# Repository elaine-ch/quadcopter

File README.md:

## Vortex 2024 Drone project

Video of it flying: [https://photos.app.goo.gl/hCnUwj7Pyiz6dDBa6](https://photos.app.goo.gl/hCnUwj7Pyiz6dDBa6)

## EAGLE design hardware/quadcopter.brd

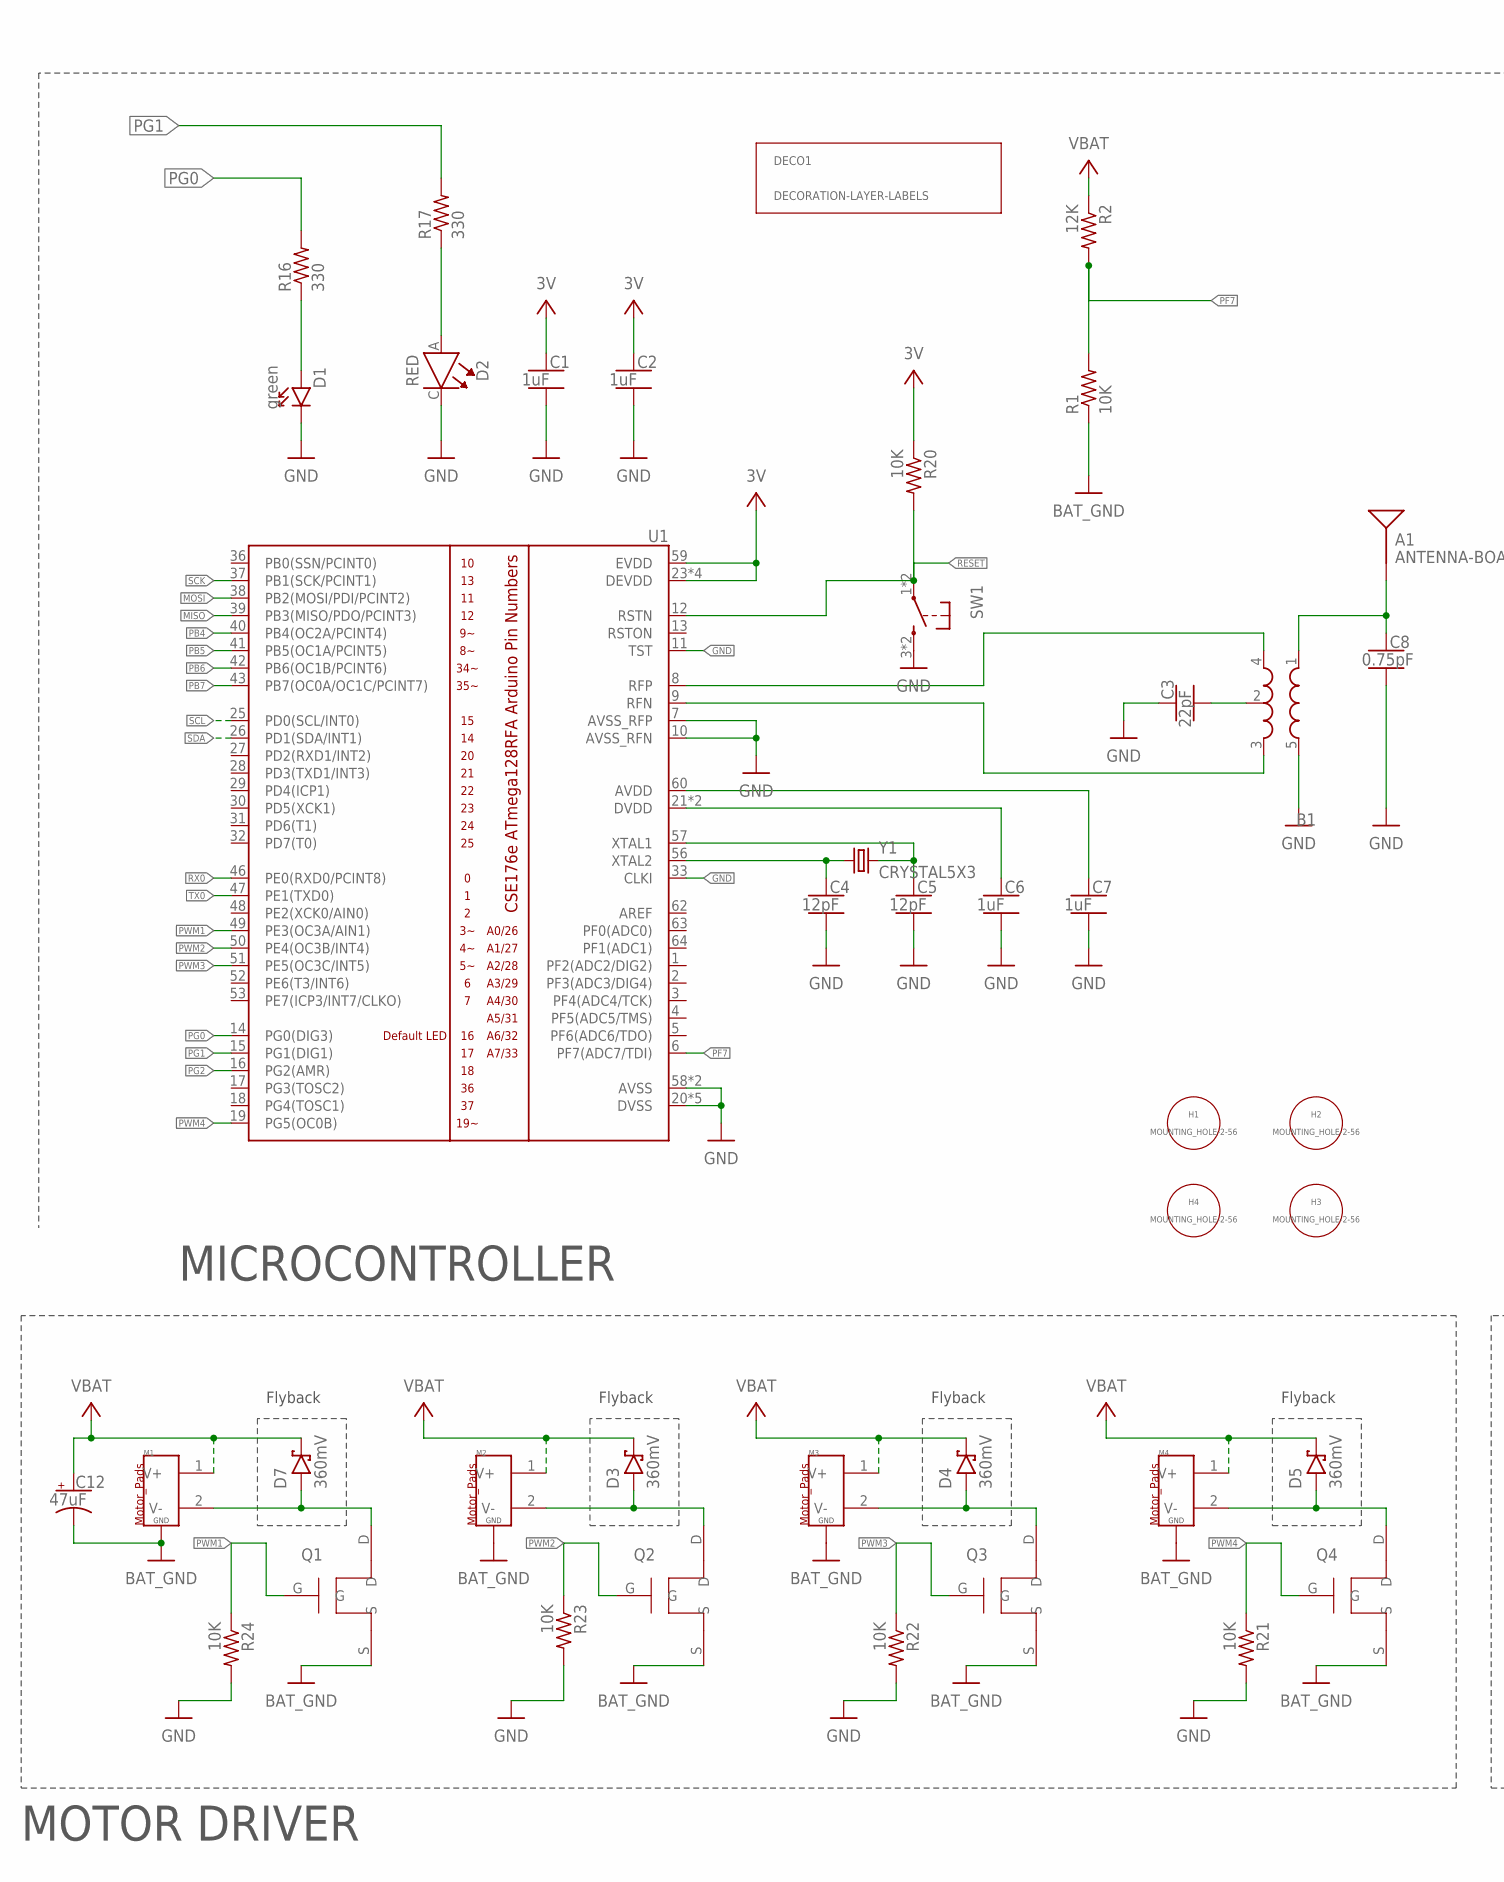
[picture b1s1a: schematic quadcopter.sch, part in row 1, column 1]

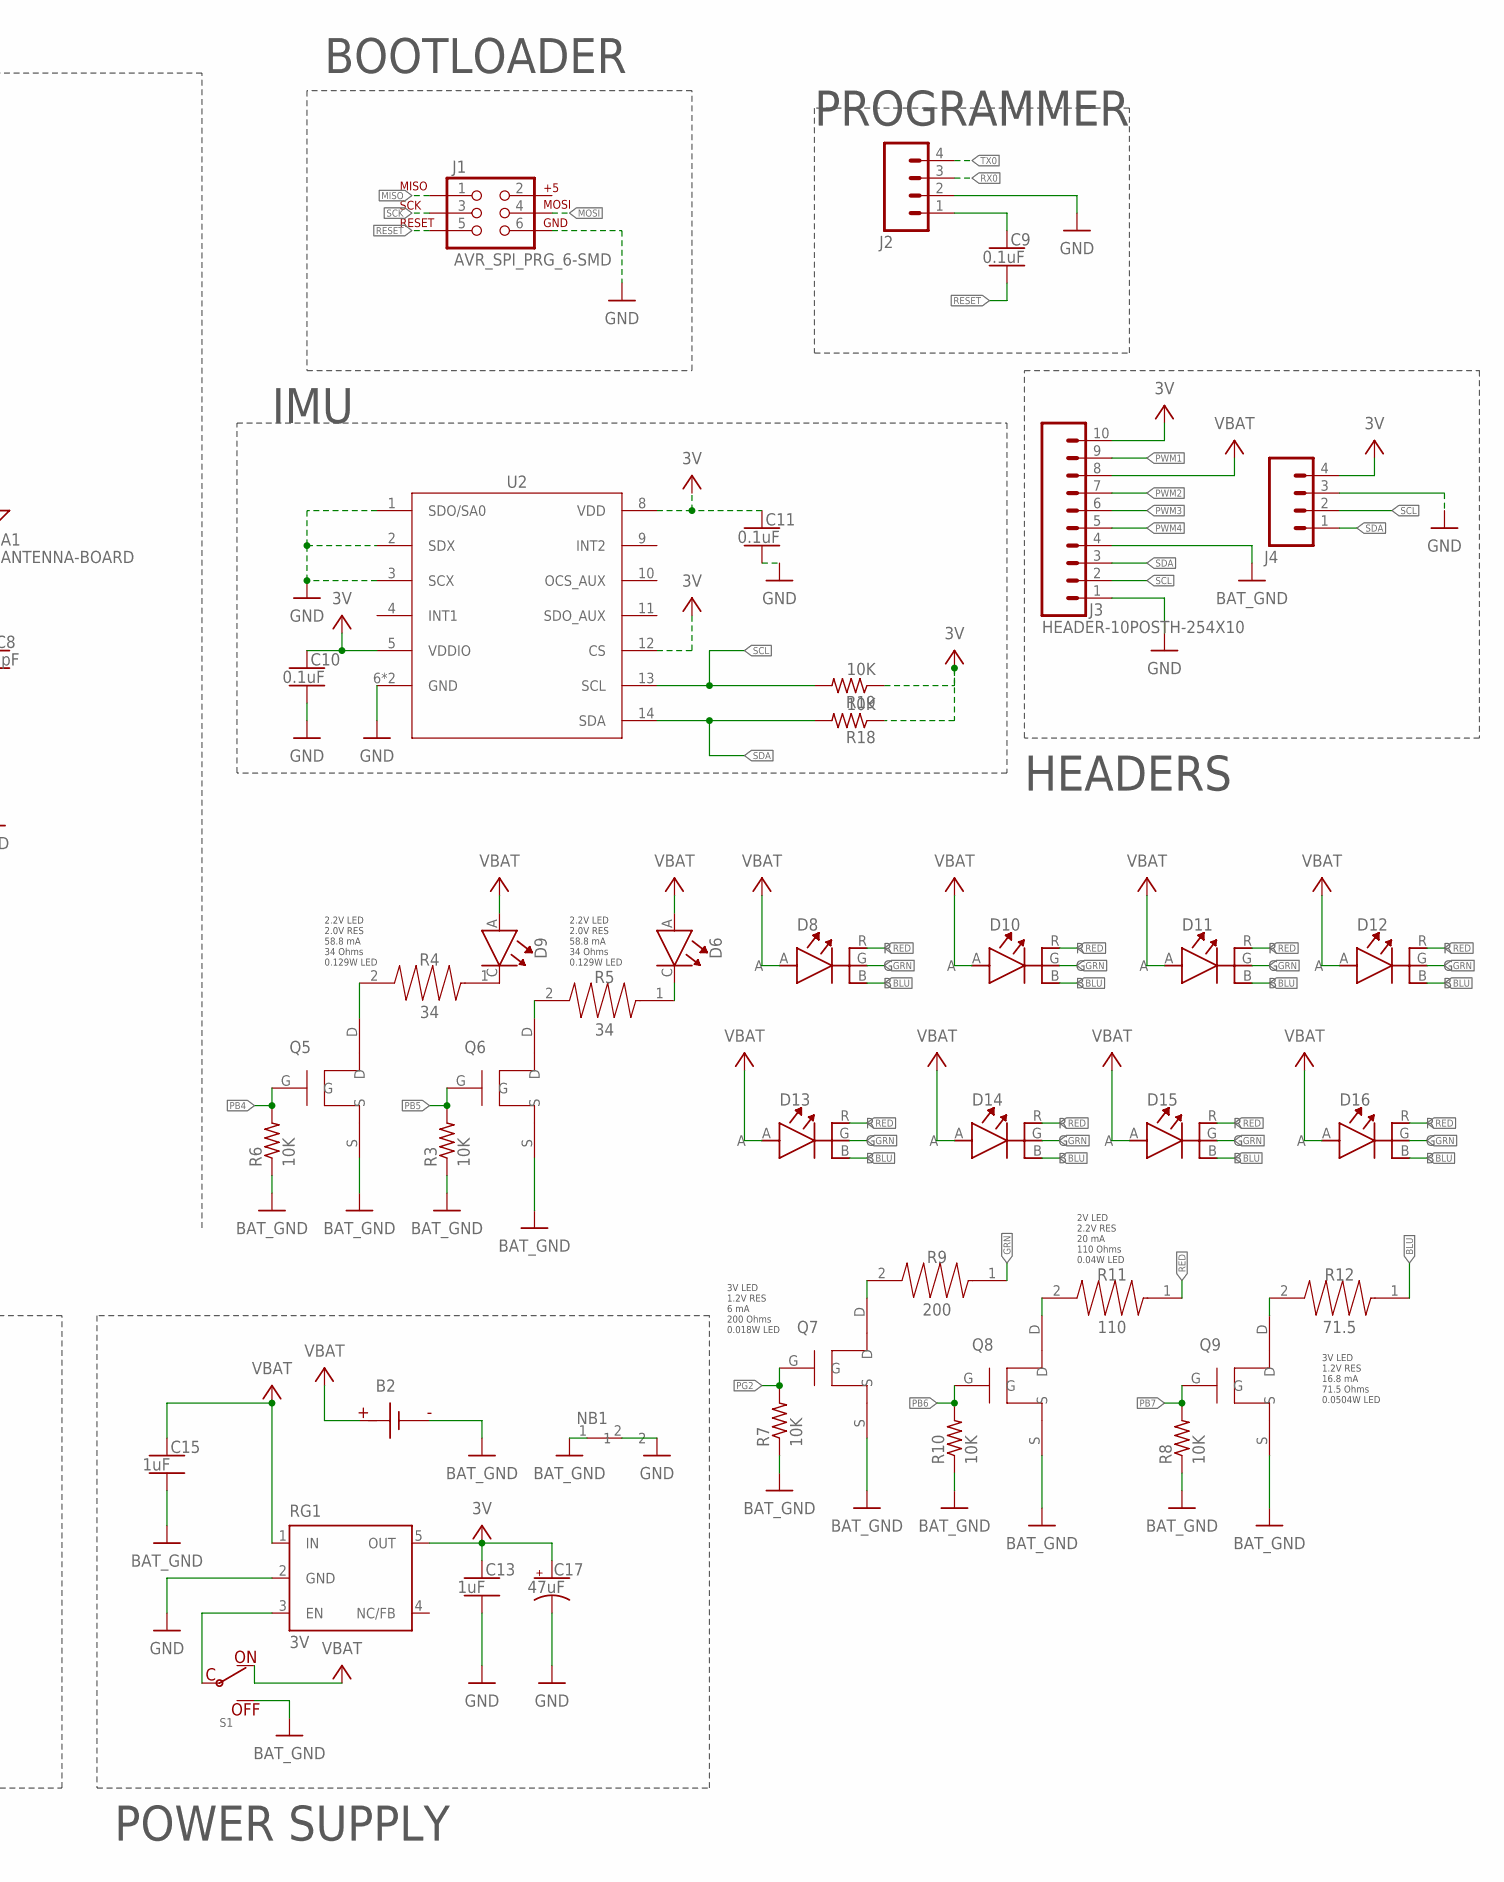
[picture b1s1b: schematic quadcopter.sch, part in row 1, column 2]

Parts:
A1: ANTENNA-BOARD; ANT_PCB_2.4GHZ_NRF8001_1.6MM_1OZ
B1: BALUN0805; BALUN
B2: BATTERY-SCREW-TERMINAL; SCREW-TERMINAL-1X2-2.54MM
C1, C2, C6, C7, C13, C15: 1uF; CAPC2012X140_HS
C3: 22pF; CAPC2012X140_HS
C4, C5: 12pF; CAPC2012X140_HS
C8: 0.75pF; CAPC2012X140_HS
C9, C10, C11: 0.1uF; CAPC2012X140_HS
C12, C17: 47uF; CAPMP3216X180
D1: green; LEDSC125X200X120-2_HS
D2: RED; LEDC1507X80
D3, D4, D5, D7: 360mV; SODFL3516X96
D6, D9: LED-YELLOW-LED; LEDQLSP30YK
D8, D10, D11, D12, D13, D14, D15, D16: RGB-LED-DIFFUSE-LED; LED150080M153000
DECO1: DECORATION-LAYER-LABELS; LAYER_LABELS
H1, H2, H3, H4: MOUNTING_HOLE-2-56; 2-56-MOUNTING-HOLE-NO-METAL
J1: AVR_SPI_PRG_6-SMD; 2X3-SMD
J2, J4: HEADER-4POS-0.1IN-FEMALE-SMD-BOTTOM-ENTRY; HEADER-1X4-BOTTOM-ENTRY
J3: HEADER-10POSTH-254X10; HDRV10W63P254_10X1_2540X254H838_HS
M1, M2, M3, M4: MOTOR_PADS_GND-MOLEX-SMD; MOLEX-0532610271
NB1: NET-BRIDGE; NET_BRIDGE
Q1, Q2, Q3, Q4, Q5, Q6, Q7, Q8, Q9: MOSFET-SI2302CDS-T1-E3CT-ND; SOT95P240X110-3MOSFET
R1, R3, R6, R7, R8, R10, R18, R19, R20, R21, R22, R23, R24: 10K; RESC2012X60_HS
R2: 12K; RESC2012X60_HS
R4, R5: 34; 0805_RESISTOR
R9: 200; 0805_RESISTOR
R11: 110; 0805_RESISTOR
R12: 71.5; 0805_RESISTOR
R16, R17: 330; RESC2012X60_HS
RG1: 3V; SOT23-DBV
S1: POWER-SWITCH-MFS201N-9-Z-SMD-EDGE; JS102011SAQN
SW1: PUSHBUTTON_SMD-VERTICAL-1; TE_FSM8JSMA_HS
U1: ATMEGA128RFA1; QFN-64
U2: LSM-IMU-497-18367-1-NDIMU; LSM6DS0-IMU
Y1: CRYSTAL5X3; CRYSTAL-SMD-5X3

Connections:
3V: C1.1, C2.1, C10.1, C11.1, C13.1, C17.1 (+), J3.10, J4.4, R18.1, R19.1, R20.1, RG1.5 (OUT), U1.23 (DEVDD), U1.34 (DEVDD), U1.44 (DEVDD), U1.54 (DEVDD), U1.59 (EVDD), U2.5 (VDDIO), U2.8 (VDD), U2.12 (CS)
BAT_GND: B2.1 (N), C12.2 (-), C15.2, J3.4, M1.G1 (GND), M1.G2 (GND), M2.G1 (GND), M2.G2 (GND), M3.G1 (GND), M3.G2 (GND), M4.G1 (GND), M4.G2 (GND), NB1.1, Q1.S, Q2.S, Q3.S, Q4.S, Q5.S, Q6.S, Q7.S, Q8.S, Q9.S, R1.1, R3.1, R6.1, R7.1, R8.1, R10.1, S1.A (OFF)
BLU: D8.B, D10.B, D11.B, D12.B, D13.B, D14.B, D15.B, D16.B, R12.1
GND: B1.5 (GND), C1.2, C2.2, C3.1, C4.2, C5.2, C6.2, C7.2, C8.2, C10.2, C11.2, C13.2, C17.2 (-), D1.C, D2.C, J1.6, J2.2, J3.1, J4.3, NB1.2, R21.2, R22.2, R23.2, R24.2, RG1.2 (GND), SW1.3 (2), SW1.4 (2), U1.7 (AVSS_RFP), U1.10 (AVSS_RFN), U1.11 (TST), U1.20 (DVSS), U1.24 (DVSS), U1.33 (CLKI), U1.35 (DVSS), U1.45 (DVSS), U1.55 (DVSS), U1.58 (AVSS), U1.61 (AVSS), U2.1 (SDO/SA0), U2.2 (SDX), U2.3 (SCX), U2.6 (GND), U2.7 (GND)
GRN: D8.G, D10.G, D11.G, D12.G, D13.G, D14.G, D15.G, D16.G, R9.1
MISO: J1.1, U1.39 (PB3(MISO/PDO/PCINT3))
MOSI: J1.4, U1.38 (PB2(MOSI/PDI/PCINT2))
unnamed: D1.A, R16.1
unnamed: D2.A, R17.1
unnamed: B1.4 (OUT1), U1.8 (RFP)
unnamed: B1.3 (OUT2), U1.9 (RFN)
unnamed: B1.2 (GND), C3.2
unnamed: C5.1, U1.57 (XTAL1), Y1.3 (2)
unnamed: C4.1, U1.56 (XTAL2), Y1.1
unnamed: C7.1, U1.60 (AVDD)
unnamed: C6.1, U1.21 (DVDD), U1.22 (DVDD)
unnamed: A1.FEED, B1.1 (IN), C8.1
unnamed: C9.1, J2.1
unnamed: D9.C, R4.1
unnamed: Q6.D, R5.2
unnamed: D7.2 (A), M1.2 (V-), Q1.D
unnamed: D3.2 (A), M2.2 (V-), Q2.D
unnamed: D4.2 (A), M3.2 (V-), Q3.D
unnamed: D5.2 (A), M4.2 (V-), Q4.D
unnamed: D6.C, R5.1
unnamed: Q7.D, R9.2
unnamed: RG1.3 (EN), S1.C
unnamed: Q8.D, R11.2
unnamed: Q5.D, R4.2
unnamed: Q9.D, R12.2
PB4: Q5.G, R6.2, U1.40 (PB4(OC2A/PCINT4))
PB5: Q6.G, R3.2, U1.41 (PB5(OC1A/PCINT5))
PB6: Q8.G, R10.2, U1.42 (PB6(OC1B/PCINT6))
PB7: Q9.G, R8.2, U1.43 (PB7(OC0A/OC1C/PCINT7))
PF7: R1.2, R2.2, U1.6 (PF7(ADC7/TDI))
PG0: R16.2, U1.14 (PG0(DIG3))
PG1: R17.2, U1.15 (PG1(DIG1))
PG2: Q7.G, R7.2, U1.16 (PG2(AMR))
PWM1: J3.9, Q1.G, R24.1, U1.49 (PE3(OC3A/AIN1))
PWM2: J3.7, Q2.G, R23.1, U1.50 (PE4(OC3B/INT4))
PWM3: J3.6, Q3.G, R22.1, U1.51 (PE5(OC3C/INT5))
PWM4: J3.5, Q4.G, R21.1, U1.19 (PG5(OC0B))
RED: D8.R, D10.R, D11.R, D12.R, D13.R, D14.R, D15.R, D16.R, R11.1
RESET: C9.2, J1.5, R20.2, SW1.1, SW1.2 (1), U1.12 (RSTN)
RX0: J2.3, U1.46 (PE0(RXD0/PCINT8))
SCK: J1.3, U1.37 (PB1(SCK/PCINT1))
SCL: J3.2, J4.2, R19.2, U1.25 (PD0(SCL/INT0)), U2.13 (SCL)
SDA: J3.3, J4.1, R18.2, U1.26 (PD1(SDA/INT1)), U2.14 (SDA)
TX0: J2.4, U1.47 (PE1(TXD0))
VBAT: B2.2, C12.1 (+), C15.1, D3.1 (C), D4.1 (C), D5.1 (C), D6.A, D7.1 (C), D8.A, D9.A, D10.A, D11.A, D12.A, D13.A, D14.A, D15.A, D16.A, J3.8, M1.1 (V+), M2.1 (V+), M3.1 (V+), M4.1 (V+), R2.1, RG1.1 (IN), S1.B (ON)

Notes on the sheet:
MICROCONTROLLER
BOOTLOADER
PROGRAMMER
Flyback
MOTOR DRIVER
POWER SUPPLY
2.2V LED 2.0V RES 58.8 mA 34 Ohms 0.129W LED
IMU
HEADERS
3V LED 1.2V RES 6 mA 200 Ohms 0.018W LED
3V LED 1.2V RES 16.8 mA 71.5 Ohms 0.0504W LED
2V LED 2.2V RES 20 mA 110 Ohms 0.04W LED

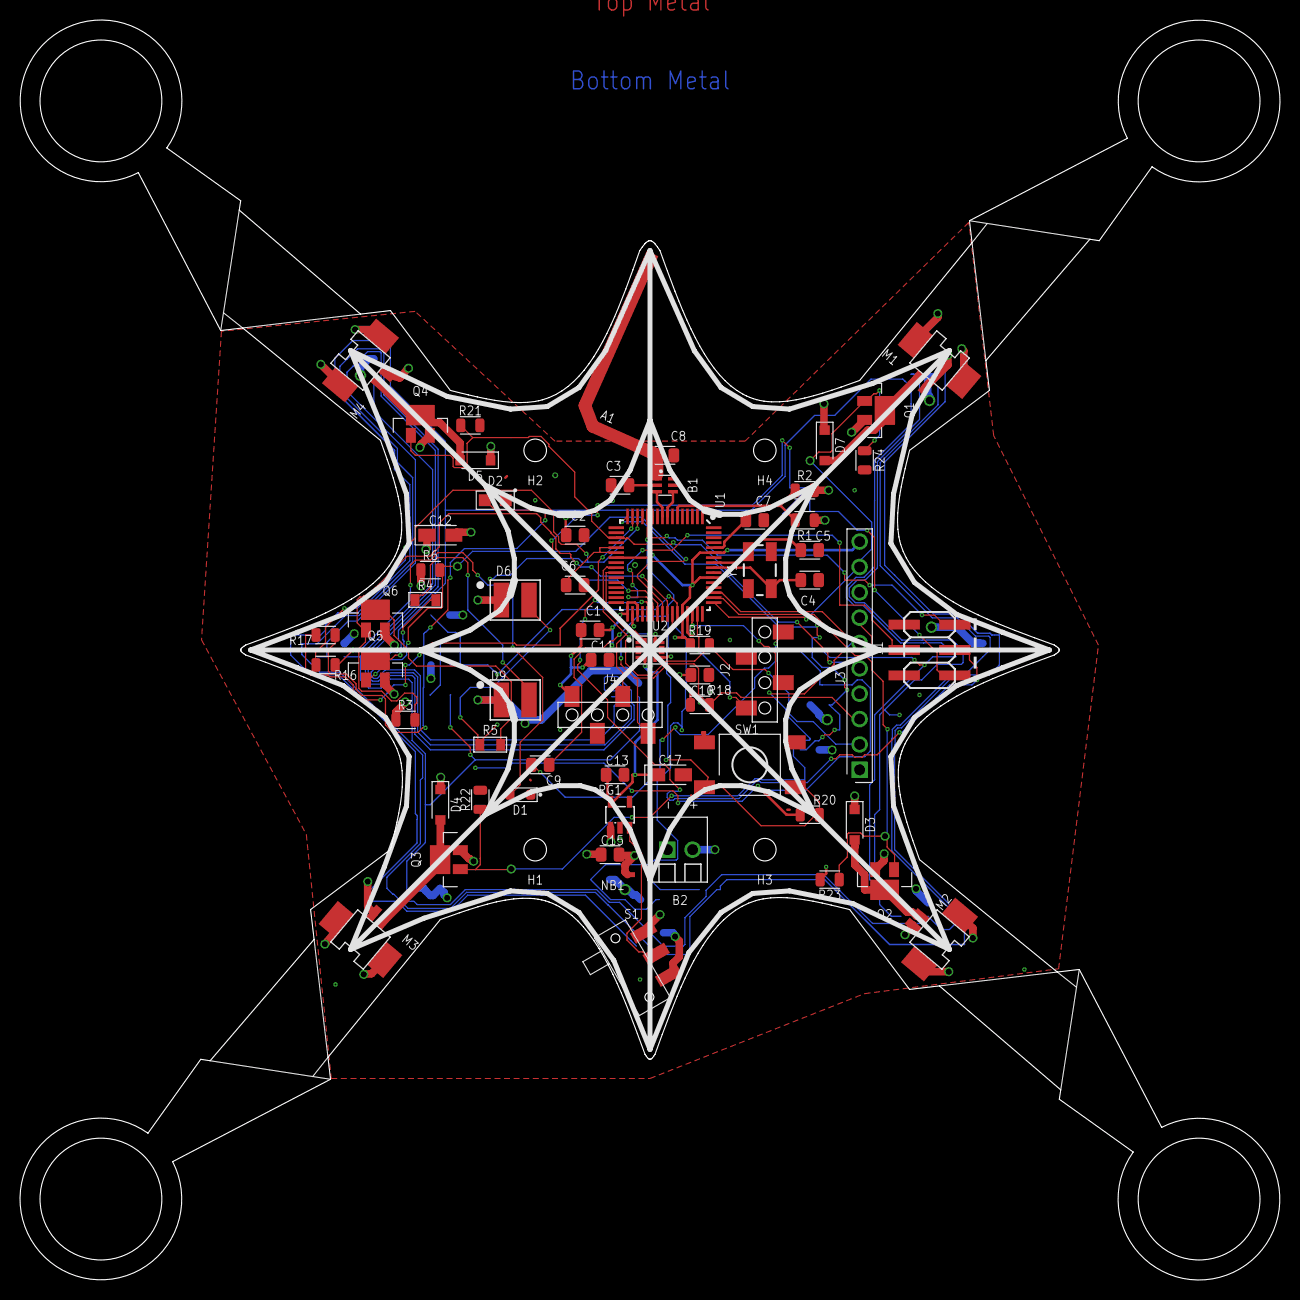
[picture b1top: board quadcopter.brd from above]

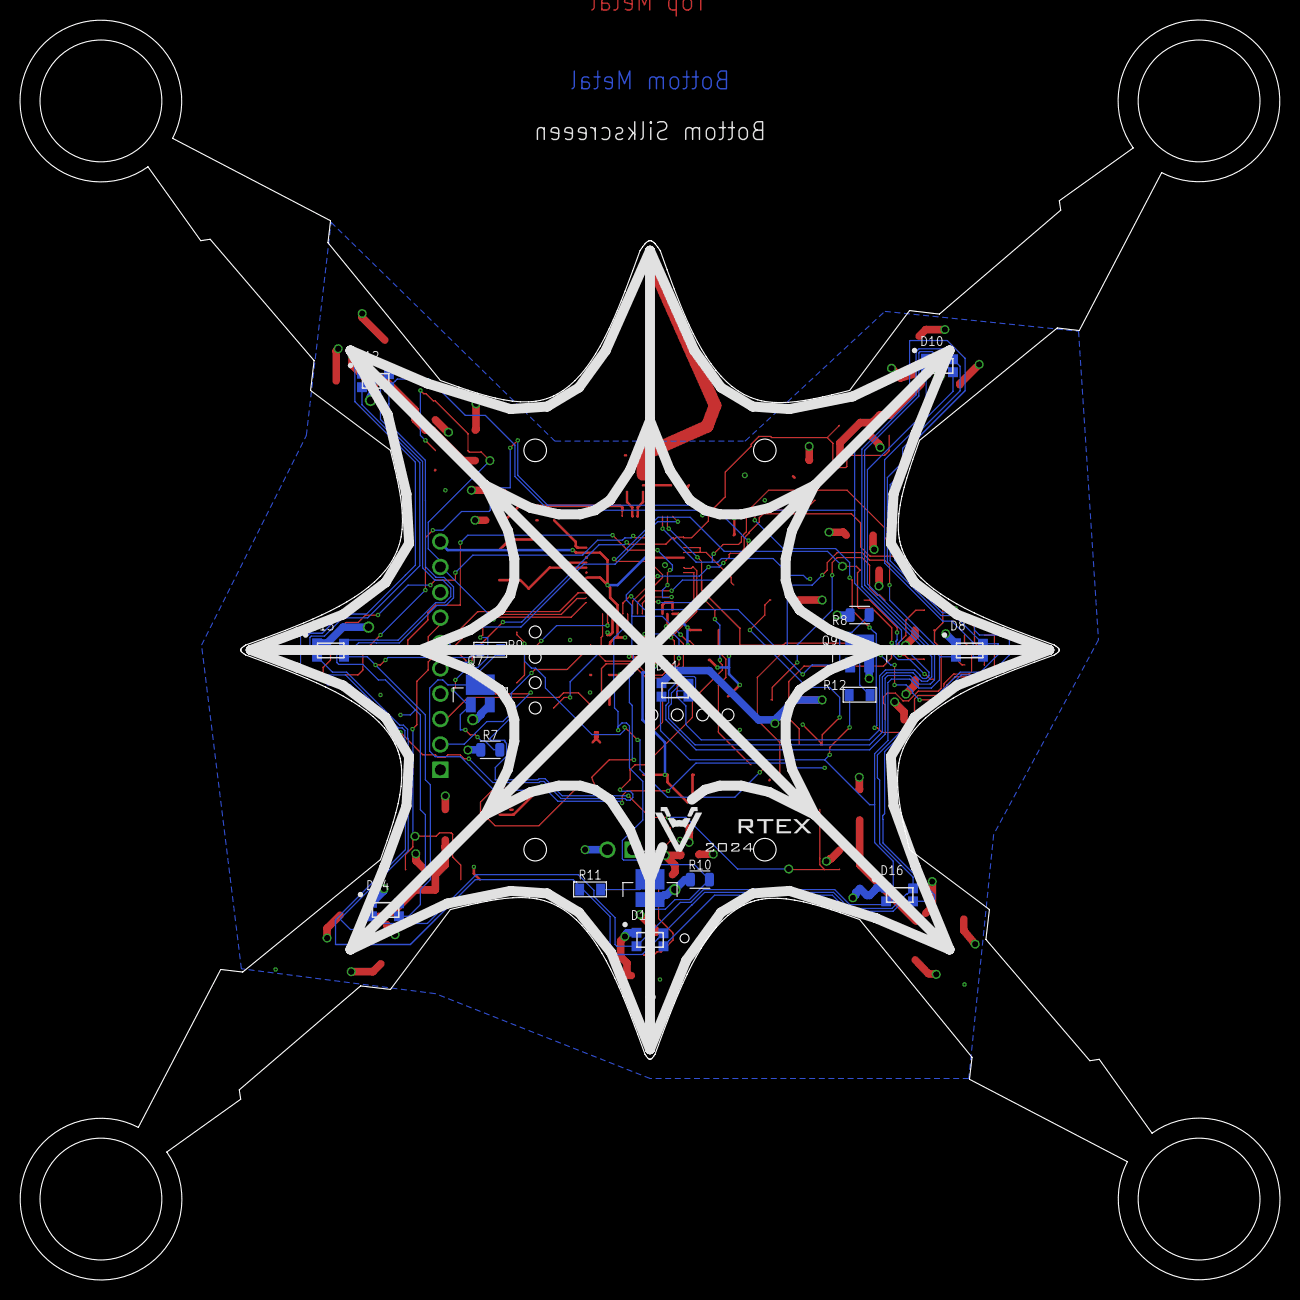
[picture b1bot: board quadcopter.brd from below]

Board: 4 copper layers, 126.2 x 126.2 mm, 85 parts (18 on the bottom side), 50 nets.

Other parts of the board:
LG1: VORTEX-LOGO

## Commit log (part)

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2024-10-10 setup
2024-10-10 added throttle serial print
2024-10-14 finished remote part 1
2024-10-15 75% of the way done
2024-10-15 FINISHED
2024-10-15 forgot to tag
2024-10-15 fixed battery levels
2024-10-15 display battery levels on LCD
2024-10-15 updated magic number
2024-10-17 Lab 3
2024-10-17 reorganized
2024-10-18 tried fixing the warnings
2024-10-18 removed .lbr
2024-10-18 updated libraries and renamed custom for submit
2024-10-18 removed extra pins
2024-10-18 switched gnd to gnd and removed VDDIO tag
2024-10-18 renamed motors
2024-10-18 fixed vddio capacitance
2024-10-18 IMU capacitances fixed?
2024-10-18 renamed net bridge
2024-10-18 fixed power supply?
2024-10-18 fixed VDDIO error hopefully
2024-10-18 copy of lbr to find
2024-10-18 fixed lbr attributes
2024-10-18 attempt to fix power supply
2024-10-18 2 new resistors
2024-10-18 resistors fixed with variants
2024-10-19 redoing lbr
2024-10-19 changed actual library name
2024-10-19 actually made the library name changes for real this time
2024-10-19 got rid of library
2024-10-19 did git reset --hard and then exported to fix battery again
2024-10-19 changed imu connection
2024-10-19 fixed n
2024-10-19 added VDDIO connection to actual VDDIO
2024-10-19 switched pull up on SCL and SDA from 'VDDIO' to 3V
2024-10-19 moved polarized capacitor by Regulator to regulated side and made out the 3V
2024-10-19 redid VDDIO
2024-10-19 renamed motor pads because mosfet is complaining?
2024-10-19 removed 3 mosfets and motor pads
2024-10-19 replaced motors
2024-10-19 replaced motor pads and mosfets fulls
2024-10-19 replaced flyback diodes
2024-10-19 why :((
2024-10-19 renamed motor pads
2024-10-19 replaced all custom resistors and parts
2024-10-19 where is my lbr
2024-10-19 added schematic oops
2024-10-19 local leds
2024-10-19 fixed errors
2024-10-19 fixed diode
2024-10-19 got rid of extra 2 1K resistors in voltage divider as suggested
2024-10-20 replaced sch to push
2024-10-20 fixed LED resistor values
2024-10-20 pushed custom library
2024-10-20 34 ohm resistors for LEDs
2024-10-20 fixed?
2024-10-22 got backlight working
2024-10-22 sensor plotting not working
2024-10-24 fixed get orientation issues
2024-10-27 added RGB LEDs
2024-10-30 placed all but RGB and supporting parts
2024-11-01 added files
2024-11-01 pushed prebuilt
2024-11-01 fixed quick check
2024-11-02 fixed quickcheck part 2
2024-11-02 changed part names
2024-11-03 fixed full check issues
2024-11-05 complimentary filter attempt 1
2024-11-05 finished fixing review
2024-11-05 fixed quick check 2
2024-11-05 fixed full check
2024-11-05 FIXED THE CAPACITORS JESUS CHRIST
2024-11-05 human error fixes and cam export
2024-11-06 one motor goes and 3 are full power or minimal power
2024-11-07 added pid set constants, need PID equations still. untested
2024-11-07 tapeout
2024-11-07 tapeout quick check update
2024-11-07 pid tuning available, no registers set, no pid actual control. cf filter appears to work
2024-11-10 implemented PID control for yaw and pitch part 1
2024-11-10 PID control fix iTerms and throttle off turns it off
2024-11-10 can do pid while armed and print pitch
2024-11-10 remote update
2024-11-11 debugging
2024-11-11 new fancy PID controls
2024-11-11 fancy PID Controls fixed (I hope)
2024-11-11 removed rad to deg
2024-11-11 flipped enc1 and button1 prev pushed
2024-11-11 can now exit PID calbration mode
2024-11-11 figured out actual correction direction
2024-11-11 constrained setting motors to between 0 and 255
2024-11-11 for leaving PID Cal mode. set button to pressed and return
2024-11-11 fix entering PID Cal Mode
2024-11-11 quad code should be good?
2024-11-11 fixed entering/exiting pid mode
2024-11-12 adding PID while armed not working
2024-11-12 working on yaw
2024-11-12 added trim
2024-11-12 got yaw working
2024-11-12 pitch working
2024-11-12 yaw working, pitch weird
2024-12-03 added roll and pin assignments
2024-12-09 added quadcopter-specific code
2024-12-09 flight on our quadcopter
2024-12-09 flipped roll to be intuitive
2024-12-10 i hate git
2024-12-10 undo the negative because that makes no sense
2024-12-10 he winks!!!!!
2024-12-10 made rgb LEDs glow
2024-12-16 after demo
